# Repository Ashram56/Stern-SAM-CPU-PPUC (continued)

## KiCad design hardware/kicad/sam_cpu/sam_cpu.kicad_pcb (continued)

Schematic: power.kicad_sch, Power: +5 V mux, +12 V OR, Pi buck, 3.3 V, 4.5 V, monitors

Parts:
C1, C2: 100u; CP_Elec_8x10
C3, C9, C10: 100n; C_0603_1608Metric
C4, C8: 100u; CP_Elec_6.3x7.7
C5: 10u; C_0805_2012Metric
C6, C7, C133, C134: 10u; C_1206_3216Metric
C135, C136: 22u; C_1206_3216Metric
C137: 100n; C_0805_2012Metric
D1: SMBJ5.0CA; D_SMB
D2: green; LED_0603_1608Metric
D4: S1M; D_SMA
D5: SMBJ15A; D_SMB
F1: 4A hold; Fuse_2920_7451Metric
FB1: 6A; L_1206_3216Metric
J11: J11 POWER; Molex_KK-396_A-41791-0006_1x06_P3.96mm_Vertical
J17: EXT 5V; TerminalBlock_Phoenix_MKDS-1,5-2-5.08_1x02_P5.08mm_Horizont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
J23: EXT 12V; TerminalBlock_Phoenix_MKDS-1,5-2-5.08_1x02_P5.08mm_Horizont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
JP1: J11 5V; SolderJumper-2_P1.3mm_Bridged_RoundedPad1.0x1.5mm
JP3: PI 5V; PinHeader_1x03_P2.54mm_Horizontal
L2: 10u; L_Changjiang_FXL0630
Q19, Q20: DMP3013SFV; Diodes_PowerDI3333-8
R1: 100k; R_0603_1608Metric
R2: 33k; R_0805_2012Metric
R3: 1k; R_0603_1608Metric
R4, R5, R7, R214: 10k; R_0805_2012Metric
R6: 33k; R_0603_1608Metric
R213: 47k; R_0603_1608Metric
R215: 100k; R_0805_2012Metric
R216: 13k; R_0603_1608Metric
TP1: +5V; TestPoint_Pad_D1.5mm
TP2: +3V3; TestPoint_Pad_D1.5mm
TP3: +4V5; TestPoint_Pad_D1.5mm
TP4: +12V; TestPoint_Pad_D1.5mm
TP5, TP6: GND; TestPoint_Pad_D1.5mm
U1: TPS2117; SOT-583-8
U3: NCP1117-3.3; SOT-223-3_TabPin2
U33, U34: LTC4412; TSOT-23-6
U35: TPS54302; SOT-23-6

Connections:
+3V3: C7.1, R3.1, TP2.1, U3.2 (VO); also elsewhere on the board
+4V5: C8.1, D4.1 (K), TP3.1; also elsewhere on the board
+5V: C4.1, C5.1, C6.1, D4.2 (A), JP3.1 (A), R4.1, TP1.1, U1.2 (VOUT), U1.7 (VOUT), U3.3 (VI); also elsewhere on the board
+12V: C2.1, C3.1, C133.1, C134.1, D5.1 (K), F1.2, R6.1, TP4.1, U35.3 (VIN); also elsewhere on the board
/Power/12V_OR: F1.1, Q19.1 (S), Q19.2 (S), Q19.3 (S), Q20.1 (S), Q20.2 (S), Q20.3 (S), U33.6 (SENSE), U34.6 (SENSE)
/Power/EXT_5V: C1.1, D1.1 (A1), J17.1, R1.1, U1.3 (VIN1), U1.5 (MODE)
/Power/EXT_12V: J23.1, Q19.5 (D), R213.1, U33.1 (VIN)
/Power/IO_12V: J11.6, Q20.5 (D), U34.1 (VIN)
/Power/J11_5V: JP1.2 (B), U1.6 (VIN2)
/Power/PI_5V_BUCK: C135.1, C136.1, JP3.3 (B), L2.2, R215.1
GND: C1.2, C2.2, C3.2, C4.2, C5.2, C6.2, C7.2, C8.2, C9.2, C10.2, C133.2, C134.2, C135.2, C136.2, D1.2 (A2), D2.1 (K), D5.2 (A), J11.2, J11.4, J11.5, J17.2, J23.2, R2.2, R5.2, R7.2, R214.2, R216.2, TP5.1, TP6.1, U1.1 (GND), U3.1 (GND), U33.2 (GND), U33.3 (CTL), U34.2 (GND), U35.1 (GND); also elsewhere on the board
unnamed: D2.2 (A), R3.2
unnamed: FB1.1, J11.1
unnamed: FB1.2, JP1.1 (A)
unnamed: Q19.4 (G), U33.5 (GATE)
unnamed: Q20.4 (G), U34.5 (GATE)
unnamed: R1.2, R2.1, U1.4 (PR1)
unnamed: R213.2, R214.1, U34.3 (CTL)
unnamed: C137.1, U35.6 (BOOT)
unnamed: R215.2, R216.1, U35.4 (FB)
unnamed: C137.2, L2.1, U35.2 (SW)
PI_5V: JP3.2 (C); also elsewhere on the board
VMON_5V: C9.1, R4.2, R5.1; also elsewhere on the board
VMON_12V: C10.1, R6.2, R7.1; also elsewhere on the board

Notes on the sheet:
4.5 V for the switch matrix
External +12 V (J23) and rail fuse F1
Test points
Supply monitors (RP2354B ADC)
3.3 V
External +5 V (J17, priority)
J11 keeps the original CPU board connector (IO board J16 harness): +5 V, ground and +12 V (pin 6, unregulated); -12 V (pin 3) is not used. The +12 V rail (audio amplifiers, Pi buck) comes from J23 (external, priority) or J11 pin 6 through ideal diodes U33 / U34 (they block reverse polarity), then F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
IO board power (J11: +5 V, +12 V on pin 6)
+12 V OR (12V_OR to F1): J23 external (priority) or J11 pin 6 (IO board)
Pi 5.1 V buck (3 A) and Pi header 5 V jumper JP3
JP3 (3-pin header, one shunt) feeds J21 pins 2 / 4 (PI_5V) from one source: 1-2: the board +5 V 2-3: the buck (Pi 4 / Pi 5, 5.18 V 3 A) no shunt: Jetson, or a Pi on its own USB-C.

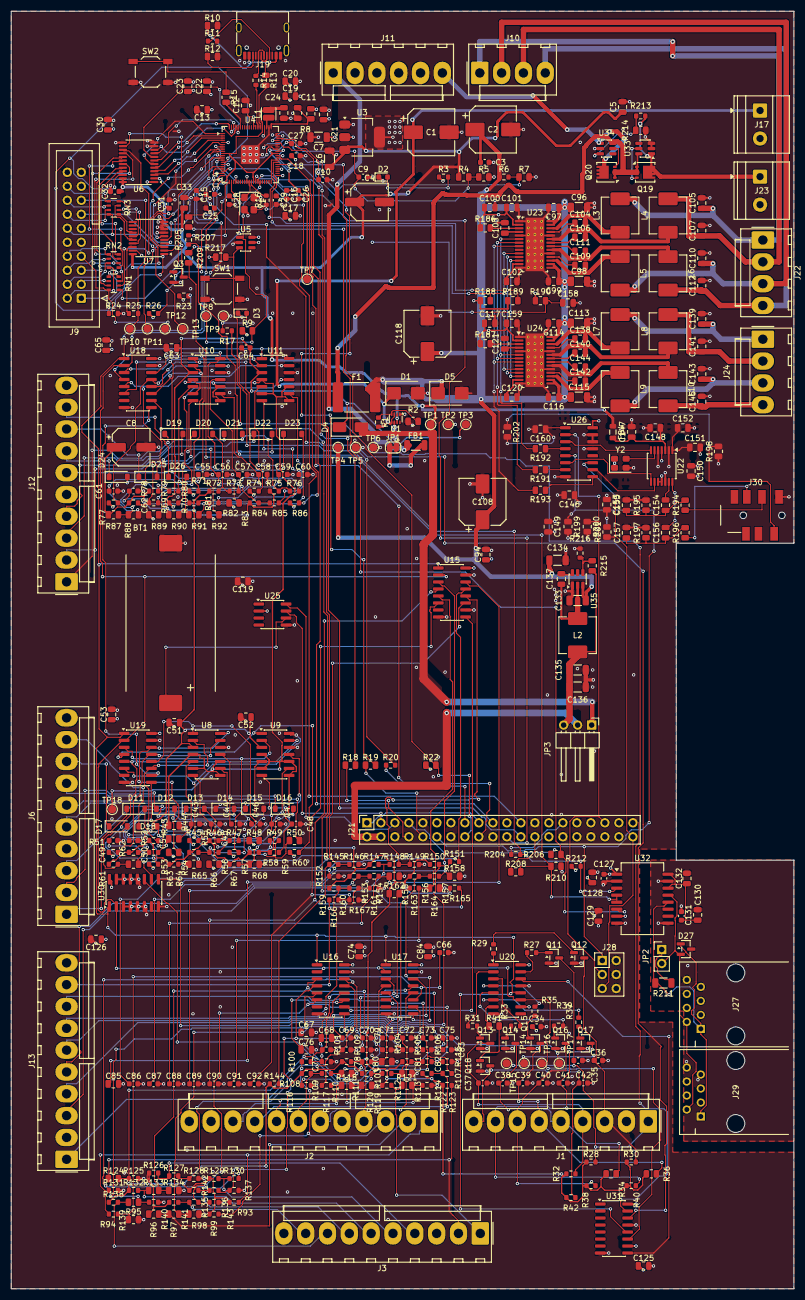
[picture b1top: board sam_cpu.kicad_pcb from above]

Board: 4 copper layers, 142.0 x 231.8 mm, 473 parts (0 on the bottom side), 320 nets.

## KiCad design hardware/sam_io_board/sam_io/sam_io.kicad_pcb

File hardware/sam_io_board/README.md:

# SAM_IO board: PPUC IO board for the Stern SAM IO power driver board

> **Revision 0.2 (branch `claude/sam-io-rp2354-dedicated`): schematic and two routed PCB options.**
> - `sam_io/`: 158 x 100 mm. J13, J3 and J2 sit on the original CPU board harness spots.
> - `sam_io_100mm/`: 100 x 100 mm. J13 on the original spot, J3 3.5 mm lower than the original spot (toward the bottom edge, for room under J2), J2 moved inboard above J3. Same schematic.
>
> Both boards put the bottom-left corner on the CPU board's bottom-left corner, with the KK-396 ramps facing inward.
> On both boards J9 stands on the left edge above J13, turned like the CPU board's J9 (pin 1 at the bottom, odd pins
> and the key notch toward the board centre), so the IO board ribbon arrives from the same side as before.
> The RP2040 and its W25Q flash are replaced by an **RP2354B** (QFN-80, 2 MB internal flash), and a new sheet
> "Dedicated switches" adds the SAM CPU board's harness connectors **J2, J3 and J13** (KK-396) with 17 input
> stages: J3 D9-D16 (flippers, EOS), J13 D17-D24 (tilt, slam, ticket notch, D20, BACK, MINUS, PLUS, SELECT) and
> the coin door memory protect on J2 pin 10. The coin slots (J2 D1-D8) are not routed. The SWD header J3 is
> renamed J20. Details: [`DESIGN.md` section 0](DESIGN.md#0-revision-02-rp2354b-and-dedicated-switches). The
> renders `sam_io/pcb_render.png` and `sam_io_100mm/pcb_render.png` show revision 0.2; the rest of this file still
> describes revision 0.1 (RP2040, 100 x 70 mm PCB).

A PPUC IO board (RP2040 on RS485) that drives a Stern SAM IO power driver board (520-5249-00) through its
CPU connector J1. It is the hardware for the `SAM_IO` board type (`PPUC_BOARD_TYPE=5`) in the io-boards
firmware (Ashram56/io-boards PR #1, `src/IODevices/SamBus/`): one board forwards every coil, flasher and lamp
of the machine to the SAM IO board's registers. It has no switch inputs and no output stage of its own.

It is derived from the PPUC **IO_16_8_1** board, version 1.1.1, by foenich
(<https://github.com/PPUC/Hardware_IO_16_8_1>, commit `46e0c47`), licensed under the
**TAPR Open Hardware License 1.0**. See [Licence](#licence-and-change-notice) below.

- [`DESIGN.md`](DESIGN.md): detailed design notes (circuit, power, reset, bus timing, signal list, BOM, PCB,
  manufacturing, bring-up).
- `sam_io/`: the KiCad 10 project (10.0 file format). Open `sam_io.kicad_pro`.
- `sam_io_100mm/`: the same project with the 100 x 100 mm board (J2 inboard).
- `sam_io_krt/`: an experiment, the same board stripped and routed again from scratch with KiCadRoutingTools,
  with a side-by-side comparison. Not the board to build.
- `sam_io/sam_io_bom.csv`: bill of materials, grouped by value and footprint.
- `sam_io/sam_io.pdf`: the two schematic sheets, for reading without KiCad.
- `sam_io/pcb_render.png`: top view of the routed board; `sam_io/pcb_copper.png`: its copper (F.Cu red, B.Cu blue).
- `original/`: the unmodified IO_16_8_1 v1.1.1 files this design was made from (KiCad 6), its PDF schematic,
  README and change log.
- `tools/`: the scripts that made the changes, for the record (see the end of this file). From now on the
  KiCad files are the source of truth: edit them in KiCad.

## What changed from IO_16_8_1

| | IO_16_8_1 | SAM_IO |
|---|---|---|
| High-power outputs (sheet OUT8) | 8 MOSFET outputs, flyback diodes, F2, 3300 µF C56, J9-J11 | **removed** |
| Inputs (sheet IN16) | 16 inputs with 2N7002 level shifters, J6-J8 | **removed**: GPIO3-18 are the SAM bus |
| SAM bus (new sheet "SAM bus") | | J9 2x10 header, SN74LVC8T245, 74AHCT541, 2N7002 for NBRESET |
| RP2040, flash, crystal, USB-C J4, SWD J3, reset / boot buttons | | unchanged |
| RS485 (ADM3483, J1, JP1-JP3 bias / termination) | | unchanged, except the 0 ohm R9 (RO to GPIO1) is now a track |
| QWIIC J2, its pull-ups R96 / R97 and C8 | | **removed** (2026-10-08) |
| Power J5 (5 V in), AP2112 3.3 V, address DIP SW3 + ladder on GPIO28, LED on GPIO25 | | unchanged |
| Special output (GPIO29 through SN74AHCT1G125 to J5 pin 5) | | unchanged (the SAM_IO firmware does not use it) |

Every part that stays keeps its reference, its position on the board and its routing.

The board is **100 x 70 mm**, the size of the PPUC Opto_16 board (99.7 x 67.3 mm) plus 2.7 mm, because the
address DIP switch SW3 sits that low on IO_16_8_1. The lower 30 mm of IO_16_8_1 held only the output stage.
The four 5.5 mm mounting holes stay at the corners, 5 mm from the edges (the top two did not move, the
bottom two moved up to y = 104 mm). They are not Opto_16's hole pattern.

## Connectors

The kept connectors are the same parts as on IO_16_8_1:

| Ref | Part | Use |
|---|---|---|
| J1 | 6-way RTM push-in terminal | RS485: 1 A, 2 B, 3 SHD, 4 A, 5 B, 6 GND (unchanged) |
| J5 | 6-way RTM push-in terminal | 1, 3, 4 = +5 V in, 2, 6 = GND, 5 = special output (unchanged) |
| J4 | USB-C | programming and debug |
| J3 | 1x3 2.54 mm (not fitted) | SWD |
| **J9** | **2x10 2.54 mm shrouded IDC header** | **SAM bus to the SAM IO board J1** |

J9 is the only new connector. It has the SAM IO board J1 pinout pin for pin, the same as J9 on the SAM CPU
replacement board, so a straight 20-way IDC ribbon (pin 1 to pin 1) connects the two:

| J9 pin | Signal | J9 pin | Signal |
|---|---|---|---|
| 1 | D3 | 2 | D4 |
| 3 | D2 | 4 | D5 |
| 5 | D1 | 6 | D6 |
| 7 | D0 | 8 | D7 |
| 9 | n.c. | 10 | n.c. |
| 11 | n.c. | 12 | A0 |
| 13 | NBRESET (open drain, active low) | 14 | A1 |
| 15 | IOSTB (active low) | 16 | A2 |
| 17 | n.c. | 18 | A3 |
| 19 | GND | 20 | GND |

The SAM IO board's J1 carries no supply, so this board is powered from J5 like every PPUC board.

## SAM bus circuit and GPIO map

The "SAM bus" sheet is a copy of the IO bus sheet of the SAM CPU replacement board
(`hardware/kicad/sam_cpu/io_bus.kicad_sch`, docs/ARCHITECTURE.md 3.1-3.2), so both boards that can drive a
SAM IO board use the same circuit:

- D0-D7: SN74LVC8T245 (U7), A side 3.3 V, B side 5 V. DIR comes from the firmware (1 = this board drives J9),
  10 k pull-down (R28).
- A0-A3 and IOSTB: 74AHCT541 (U8) at 5 V, TTL inputs. Unused inputs tied low.
- Both buffers share BUS_OE_N with a 10 k pull-up (R27): off at power-up, so the SAM IO board's own pull-ups
  hold IOSTB high and nothing latches while the RP2040 boots.
- NBRESET: 2N7002 (Q1) open drain against the SAM IO board's 10 k pull-up. Its gate has a 10 k pull-up (R30),
  so the SAM IO board is held in reset (all outputs off) until the firmware lets go.
- 33 R in series on every J9 line (RN1-RN3, R29), for the ribbon cable.
- Test points TP3 IOSTB, TP4 NBRESET, TP5 D0, TP6 A0.

The GPIOs match `src/IODevices/SamBus/SamBusPins.h` in io-boards exactly, so the firmware needs no change:

| GPIO | Signal | GPIO | Signal |
|---|---|---|---|
| 0, 1, 2 | RS485 TX, RX, DE (unchanged) | 15 | BUS_IOSTB |
| 3-10 | BUS_D0-D7 | 16 | BUS_DIR |
| 11-14 | BUS_A0-A3 | 17 | BUS_OE_N (low = buffers on) |
| 25 | status LED (unchanged) | 18 | NBRESET_DRV (high = SAM IO board in reset) |
| 28 | board id ladder, DIP SW3 (unchanged) | 29 | special output (unchanged) |
| 19-24, 26, 27 | not connected (were Out_1-Out_8) | | |

Revision 0.2 (RP2354B) keeps GPIO0-18, 25 and 29 as above and adds:

| GPIO | Signal | GPIO | Signal |
|---|---|---|---|
| 19-24, 26, 27 | DED_D17-D24 (J13: tilt, slam, ticket notch, D20, BACK, MINUS, PLUS, SELECT) | 38 | MEM_PROTECT (J2 pin 10, coin door) |
| 30-37 | DED_D9-D16 (J3: flipper buttons and EOS) | 40 (ADC0) | board id ladder, DIP SW3 (was GPIO28: the RP2354B's ADC is on GPIO40-47) |
| 28, 39, 41-47 | not connected | | |

All dedicated inputs are active low (switch closed = 0).

## Checks

- ERC (KiCad 10.0.6): 2 errors and 9 warnings, all inherited from IO_16_8_1 (ADC_AVDD and +5 V power-flag
  warnings, +5 V / VCC net name on U5, library symbols that differ from the KiCad 10 libraries). Nothing on the
  new sheet.
- The netlist was compared pin by pin with the original: every kept part keeps its nets, except the RP2040
  GPIO3-18 (now the bus) and GPIO19-24, 26, 27 (now unconnected).
- DRC: fully routed (no unconnected item), no new violation. The remaining items are the original's (USB-C J4
  pad to slot clearance, J2 / C8 courtyards, starved thermals on J4, U5 and C8, footprints that differ from the
  KiCad 10 libraries). Design rules are unchanged: 0.2 mm tracks and clearance, 0.5 / 0.3 mm vias.
- Schematic parity: no net differences. KiCad lists field differences (datasheet links, test point BOM flag)
  that one "Update PCB from Schematic" in KiCad clears.

## Open points

Nothing below blocks reviewing the design; the first group blocks ordering boards, the rest is to check on the
bench or to tidy up later. [DESIGN.md](DESIGN.md) has the details behind each one.

Before ordering:

- **Fabrication files**: no Gerbers, drill files or pick-and-place file yet. Generate them from KiCad (or
  `kicad-cli pcb export gerbers / drill / pos`) once the points below are settled.
- **Update PCB from Schematic**: run it once in KiCad to clear the remaining field differences (datasheet links,
  test point BOM flag). No net changes are expected; re-run DRC afterwards.
- **C31 via in pad**: there was no room for a GND via beside C31 (U7's 5 V decoupling), so its GND pad has
  one. Ask the fab for a filled or tented via, or check the solder joint.
- **Mounting holes**: the four corner holes of the 100 x 70 mm outline follow neither IO_16_8_1 nor Opto_16.
  Check where the board will sit in the machine (or on the SAM IO board's ribbon) and move them if needed.
- **Parts availability**: check stock for the new parts (SN74LVC8T245 in TSSOP-24, 74AHCT541 in TSSOP-20, 2N7002,
  4 x 33 R arrays, 2 x 10 IDC header) at the assembler; the BOM is `sam_io/sam_io_bom.csv`.

On the bench:

- **Bus timing against a real SAM IO board** (ARCHITECTURE.md Q4): setup, IOSTB width and hold as set by the
  firmware (140 / 175 / 245 ns), the STATUS read turnaround (DIR flip and U7 delay inside the read window),
  and edge quality on the 22 pF lines through the series resistors.
- **Watchdog and reset**: the SAM IO board must stay in reset while the RP2040 boots and come out of it only
  once lamp strobes run (DRV0 within 62.5-250 ms); NBRESET held low long enough for the DS1232 (about 20 ms).
- **Ribbon**: the 20-way cable carries only two GND wires; keep it short, check pin-1 orientation on both ends
  and the ground return under full lamp load.
- **5 V supply**: confirm which 5 V the board takes in the machine and that its ground is shared with the SAM
  IO board's logic ground.
- **Firmware**: the `SAM_IO` board type is in Ashram56/io-boards PR #1, still open. Board type `0x05` is a
  proposal to agree with PPUC upstream.

Later, if wanted:

- **References reused**: J9, Q1, R27-R30 and C30-C33 were IO_16_8_1 input / output parts and are now SAM bus
  parts (matching the CPU board's J9). Compare with `original/` by function, not by reference. A re-annotation
  would remove the confusion but break the comparison.
- **Spare resources**: RP2040 GPIO19-24, 26, 27 are unconnected and U8 has three unused channels (inputs tied
  to GND). They could carry the 20 V / 50 V interlock inputs or GI relay control later.
- **Library footprints**: several footprints inherited from IO_16_8_1 differ from the KiCad 10 libraries (DRC
  warnings only). Update them from the library if the board is reworked.
- **Copper tidy-up**: a few short GND tracks between stitching vias on B.Cu are left from IO_16_8_1's routing;
  harmless inside the pour, removable.

## Routing

Two layers, as on IO_16_8_1. The parts that stayed keep their routing; the SAM bus parts sit on the left, where
the input stage was:

- J9 on the left edge, RN1-RN3 and R29 next to it, then U7 (data) above U8 (address and IOSTB), close to the
  RP2040.
- RP2040 to buffers, routed by hand (`tools/c08_bus_fanout.py`). The RP2040 and both buffers number their pins
  anticlockwise, so a bus that keeps its bit order between them has to cross itself once. Each of the 13 lines
  leaves the RP2040 on the top layer (reusing IO_16_8_1's GPIO fanout next to the chip), drops through a via
  under its own buffer pin and crosses under the others on the bottom layer, then comes back up to the pin:
  two vias per line. DIR, OE_N and NBRESET_DRV reuse IO_16_8_1's GPIO16-18 fanout down the right of the RP2040.
- Buffers to J9, pull-ups and power: Freerouting 2.5, with every existing track locked, then a few touch-ups
  (`tools/c09_route_fixes.py`).
- GND is the pour on both layers, as before.

## Licence and change notice

This design is a modification of PPUC IO_16_8_1 v1.1.1 by foenich and is licensed, like the original, under the
**TAPR Open Hardware License 1.0** ([`LICENSE-TAPR-OHL.txt`](LICENSE-TAPR-OHL.txt), an unaltered copy). It is
not covered by the repository's CERN-OHL-S licence. The modifications are licensed under the terms of the TAPR
OHL.

Elements changed (TAPR OHL 4.2a):
- `IO_16_8_1.kicad_sch` -> `sam_io/sam_io.kicad_sch`: IN16 and OUT8 sheets and their labels removed; GPIO3-18
  labels renamed to the SAM bus global labels; no-connect flags on GPIO19-24, 26, 27; "SAM bus" sheet added;
  title block and a change note; file upgraded to KiCad 10.
- `IN16.kicad_sch`, `OUT8.kicad_sch`: removed.
- `sam_io/sam_bus.kicad_sch`: new (from the SAM CPU replacement board's IO bus sheet).
- `IO_16_8_1.kicad_pcb` -> `sam_io/sam_io.kicad_pcb`: IN16 / OUT8 footprints, their tracks and vias, the GNDPWR
  zone and the J6-J11 / fuse silkscreen removed; GND zone extended over the freed area; board name changed to
  "PPUC SAM_IO"; SAM bus parts added and routed; outline cut to 100 x 70 mm, bottom mounting holes, logo and
  board name moved up, copper below the new edge removed; file upgraded to KiCad 10.
- `IO_16_8_1.kicad_pro` -> `sam_io/sam_io.kicad_pro`: renamed, upgraded to KiCad 10.
- `logo.kicad_sym`, `IO_16_8_1.pretty`, `fp-lib-table`, `sym-lib-table`, `PPUC-Logo-PCB-230129.svg`: unchanged.

The original versions of the changed files are in `original/` (TAPR OHL 4.2b). The original documentation names
no licensor e-mail address, so section 3 asks nothing further. Before boards are made, add the Gerber and drill
files to this folder (TAPR OHL 4.2d).

## How the changes were made

`tools/c01_root_sheet.py` and `tools/c02_sam_bus_sheet.py` edited the schematic sheets.
`tools/run.sh` rebuilt the board from the original with `c03_board_update.py` (remove / add footprints, KiCad 10
Python), `c04_board_clean.py` (tracks, zones and silkscreen, on the file text) and `c05_drc_via_cleanup.py`
(leftover vias reported by DRC). `tools/run_route.sh` then made the 100 x 70 mm outline and the routing:
`c06_outline_placement.py` (outline, holes, placement), `c07_trim_copper.py` (copper below the new edge),
`c08_bus_fanout.py` (RP2040 side of the bus), two Freerouting passes (`route_mkdsn.py`, `route_import.py`),
`c09_route_fixes.py` and `c10_silk.py`. Do not rerun them over the current files.

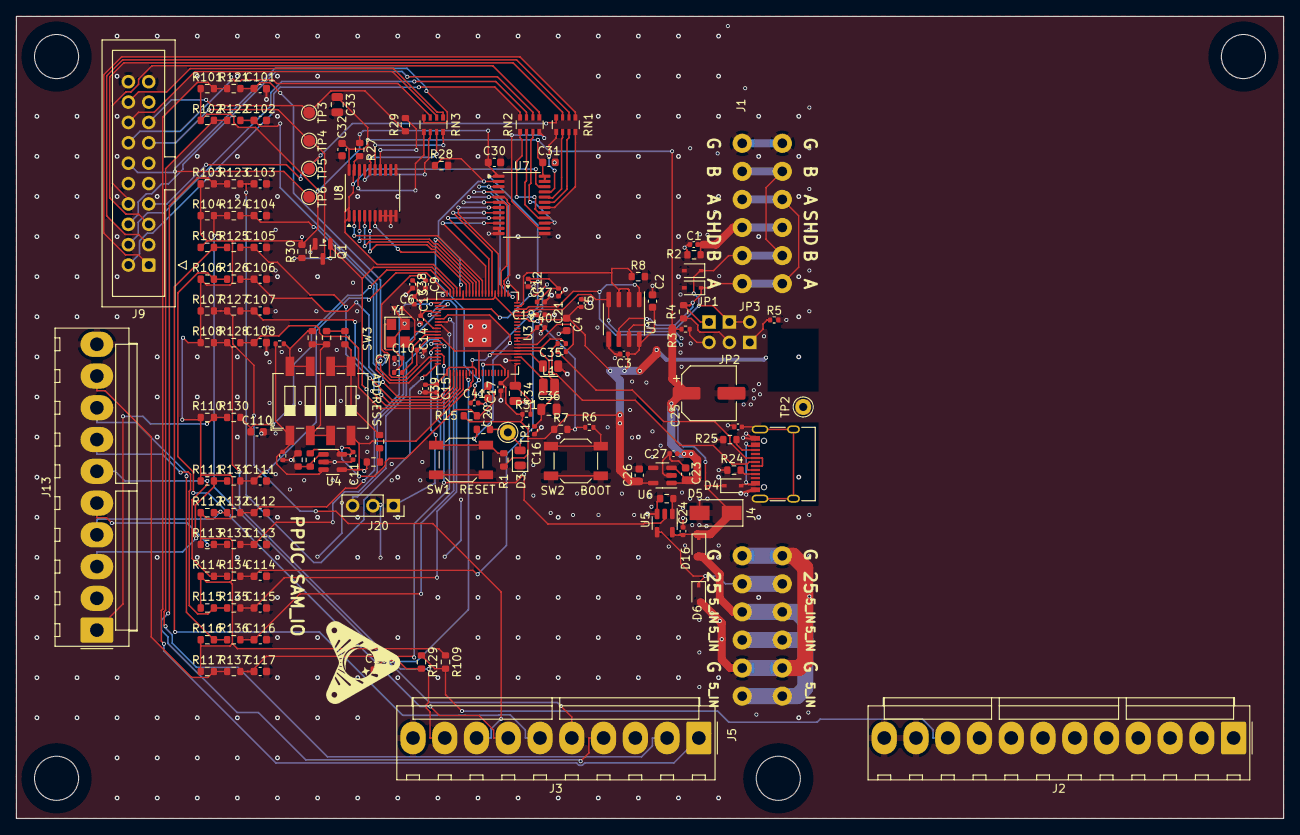
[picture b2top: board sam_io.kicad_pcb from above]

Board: 2 copper layers, 158.0 x 100.0 mm, 158 parts (0 on the bottom side), 123 nets.

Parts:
C1, C3, C5, C9, C10, C11, C12, C13, C14, C15, C17, C19, C22, C24, C27, C37, C38, C39, C40, C41: 100n; C_0402_1005Metric
C2, C4, C20, C23, C26: 10u; C_0603_1608Metric
C6, C7: 27pF; C_0402_1005Metric
C16, C21: 1u; C_0402_1005Metric
C25: 100µ 16V; CP_Elec_6.3x5.4
C30, C31, C32: 100n; C_0603_1608Metric
C33: 10u; C_0805_2012Metric
C34, C35, C36: 4.7u; C_0805_2012Metric
C101, C102, C103, C104, C105, C106, C107, C108, C109, C110, C111, C112, C113, C114, C115, C116, C117: 1n; C_0603_1608Metric
D1, D2: SD15; D_SOD-323
D3: LED gn; LED_0805_2012Metric
D4, D16: 1A; D_SOD-323
D5: SMAJ5.0; D_SMA
D6: SD05; D_SOD-323
J1, J5: Conn_01x06; Terminal_Block_RTMPin
J2: J2 DEDICATED D1-D8; Molex_KK-396_A-41791-0012_1x12_P3.96mm_Vertical
J3: J3 DEDICATED D9-D16; Molex_KK-396_A-41791-0010_1x10_P3.96mm_Vertical
J4: USB_C_Receptacle_USB2.0; USB_C_Receptacle_XKB_U262-16XN-4BVC11
J9: SAM BUS; IDC-Header_2x10_P2.54mm_Vertical
J13: J13 DEDICATED D17-D24; Molex_KK-396_A-41791-0010_1x10_P3.96mm_Vertical
J20: nmount SW Debug; PinSocket_1x03_P2.54mm_Vertical
JP1, JP2, JP3: Jumper_2_Open; PinHeader_1x02_P2.54mm_Vertical
L1: 3.3u; L_Cenker_CKCS201610
Q1: 2N7002; SOT-23
R1, R7, R8, R26, R27, R28, R30, R121, R122, R123, R124, R125, R126, R127, R128, R129, R130, R131, R132, R133, R134, R135, R136, R137: 10k; R_0603_1608Metric
R2, R15: 100R; R_0603_1608Metric
R3, R5: 620; R_0402_1005Metric
R4: 120R; R_0603_1608Metric
R6, R12, R16, R20: 1k; R_0402_1005Metric
R10, R11: 27; R_0402_1005Metric
R13: 33k; R_0603_1608Metric
R14, R18, R19, R23: 2k; R_0603_1608Metric
R17: 5k; R_0603_1608Metric
R21: 470; R_0603_1608Metric
R22: 3k; R_0603_1608Metric
R24, R25: 5k1; R_0603_1608Metric
R29: 33; R_0603_1608Metric
R31: 33; R_0402_1005Metric
R101, R102, R103, R104, R105, R106, R107, R108, R109, R110, R111, R112, R113, R114, R115, R116, R117: 1k; R_0603_1608Metric
RN1, RN2, RN3: 33; R_Array_Convex_4x0603
SW1: Reset; SW_SPST_SKQG_WithStem
SW2: Boot; SW_SPST_SKQG_WithStem
SW3: ADDRESS; SW_DIP_SPSTx04_Slide_6.7x11.72mm_W8.61mm_P2.54mm_LowProfile
TP1: TP_LED; Pin_D1.0mm_L10.0mm
TP2: TP_GND; Pin_D1.0mm_L10.0mm
TP3: J9_IOSTB; TestPoint_Pad_D1.5mm
TP4: J9_NBRESET; TestPoint_Pad_D1.5mm
TP5: J9_D0; TestPoint_Pad_D1.5mm
TP6: J9_A0; TestPoint_Pad_D1.5mm
U1: ADM3483; SOIC-8_3.9x4.9mm_P1.27mm
U3: RP2354B; QFN-80-1EP_10x10mm_P0.4mm_EP3.4x3.4mm
U4: LMV321; SOT-23-5
U5: SN74AHCT1G125; SOT-23-5
U6: AP2112K-3.3; SOT-23-5
U7: SN74LVC8T245; TSSOP-24_4.4x7.8mm_P0.65mm
U8: 74AHCT541; TSSOP-20_4.4x6.5mm_P0.65mm
Y1: 12MHz,18pF; Crystal_SMD_3225-4Pin_3.2x2.5mm

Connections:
+3V3: C2.1, C3.1, C4.1, C5.1, C12.1, C13.1, C14.1, C15.1, C17.1, C19.1, C21.1, C26.1, C30.1, C35.1, C37.1, C38.1, C39.1, C40.1, R1.2, R7.1, R15.1, R27.1, R30.1, R31.1, R101.1, R102.1, R103.1, R104.1, R105.1, R106.1, R107.1, R108.1, R109.1, R110.1, R111.1, R112.1, R113.1, R114.1, R115.1, R116.1, R117.1, U1.8 (VCC), U3.5, U3.15, U3.24, U3.29, U3.41, U3.50, U3.60, U3.64, U3.68, U3.69, U3.76, U6.5 (VOUT), U7.1
+5V: C23.1, C24.1, C25.1, C27.1, C31.1, C32.1, C33.1, D4.1 (K), D5.1 (K), D16.1 (K), R3.1, U5.5 (VCC), U6.1 (VIN), U6.3 (EN), U7.23, U7.24, U8.20
/1V1: C9.1, C10.1, C16.1, C36.1, C41.1, L1.2, U3.10, U3.32, U3.51, U3.65
/3V3A: C11.1, C20.1, R13.1, R15.2, U3.59, U4.5 (V+)
/5V_IN: D16.2 (A), J5.1, J5.3, J5.4
/485_DE: R8.2, U1.2 (~RE), U1.3 (DE), U3.79
/485_RX: U1.1 (RO), U3.78
/485_TX: U1.4 (DI), U3.77
/A: D1.1 (K), J1.1, J1.4, JP1.1 (A), R4.1, U1.6 (A)
/B: D2.1 (K), J1.2, J1.5, JP2.1 (A), JP3.2 (B), U1.7 (B)
/Dedicated switches/IN_D9: J3.1, R101.2, R121.1
/Dedicated switches/IN_D10: J3.2, R102.2, R122.1
/Dedicated switches/IN_D11: J3.4, R103.2, R123.1
/Dedicated switches/IN_D12: J3.5, R104.2, R124.1
/Dedicated switches/IN_D13: J3.6, R105.2, R125.1
/Dedicated switches/IN_D14: J3.7, R106.2, R126.1
/Dedicated switches/IN_D15: J3.8, R107.2, R127.1
/Dedicated switches/IN_D16: J3.9, R108.2, R128.1
/Dedicated switches/IN_D17: J13.1, R110.2, R130.1
/Dedicated switches/IN_D18: J13.3, R111.2, R131.1
/Dedicated switches/IN_D19: J13.4, R112.2, R132.1
/Dedicated switches/IN_D20: J13.5, R113.2, R133.1
/Dedicated switches/IN_D21: J13.6, R114.2, R134.1
/Dedicated switches/IN_D22: J13.7, R115.2, R135.1
/Dedicated switches/IN_D23: J13.8, R116.2, R136.1
/Dedicated switches/IN_D24: J13.9, R117.2, R137.1
/Dedicated switches/IN_MEMPROT: J2.10, R109.2, R129.1
/Out_S: D6.1 (K), J5.5, U5.4
/Out_Special: U3.37, U5.2
/Q_nCS: R6.2, R7.2, U3.75
/SHD: C1.1, J1.3, R2.1
/SWCLK: J20.1, U3.33
/SWDIO: J20.3, U3.34
/USB_D+: J4.A6 (D+), J4.B6 (D+), R10.1
/USB_D-: J4.A7 (D-), J4.B7 (D-), R11.1
/USB_DM_MCU: R11.2, U3.66
/USB_DP_MCU: R10.2, U3.67
/VREG_AVDD: C34.1, R31.2, U3.61
/VREG_LX: L1.1, U3.63
/V_addr: R17.1, SW3.4, U3.49, U4.4
/XIN: C6.2, U3.30, Y1.3
/XOUT: R12.2, U3.31
/nReset: R1.1, SW1.2, U3.35
BUS_A0: U3.9, U8.2
BUS_A1: U3.11, U8.3
BUS_A2: U3.12, U8.4
BUS_A3: U3.13, U8.5
BUS_D0: U3.80, U7.3
BUS_D1: U3.1, U7.4
BUS_D2: U3.2, U7.5
BUS_D3: U3.3, U7.6
BUS_D4: U3.4, U7.7
BUS_D5: U3.6, U7.8
BUS_D6: U3.7, U7.9
BUS_D7: U3.8, U7.10
BUS_DIR: R28.1, U3.16, U7.2
BUS_IOSTB: U3.14, U8.6
BUS_OE_N: R27.2, U3.17, U7.22, U8.1, U8.19
DED_D9: C101.1, R121.2, U3.38
DED_D10: C102.1, R122.2, U3.39
DED_D11: C103.1, R123.2, U3.40
DED_D12: C104.1, R124.2, U3.42
DED_D13: C105.1, R125.2, U3.43
DED_D14: C106.1, R126.2, U3.44
DED_D15: C107.1, R127.2, U3.45
DED_D16: C108.1, R128.2, U3.46
DED_D17: C110.1, R130.2, U3.19
DED_D18: C111.1, R131.2, U3.20
DED_D19: C112.1, R132.2, U3.21
DED_D20: C113.1, R133.2, U3.22
DED_D21: C114.1, R134.2, U3.23
DED_D22: C115.1, R135.2, U3.25
DED_D23: C116.1, R136.2, U3.27
DED_D24: C117.1, R137.2, U3.28
GND: C1.2, C2.2, C3.2, C4.2, C5.2, C6.1, C7.1, C9.2, C10.2, C11.2, C12.2, C13.2, C14.2, C15.2, C16.2, C17.2, C19.2, C20.2, C21.2, C22.2, C23.2, C24.2, C25.2, C26.2, C27.2, C30.2, C31.2, C32.2, C33.2, C34.2, C35.2, C36.2, C37.2, C38.2, C39.2, C40.2, C41.2, C101.2, C102.2, C103.2, C104.2, C105.2, C106.2, C107.2, C108.2, C109.2, C110.2, C111.2, C112.2, C113.2, C114.2, C115.2, C116.2, C117.2, D1.2 (A), D2.2 (A), D3.1 (K), D5.2 (A), D6.2 (A), J1.6, J2.11, J2.12, J3.10, J4.A1 (GND), J4.A12 (GND), J4.B1 (GND), J4.B12 (GND), J5.2, J5.6, J9.19, J9.20, J13.10, J20.2, Q1.2, R2.2, R5.2, R8.1, R14.2, R16.2, R24.2, R25.2, R26.2, R28.2, SW1.1, SW2.1, TP2.1, U1.5 (GND), U3.62, U3.81, U4.2 (V-), U5.3 (GND), U6.2 (GND), U7.11, U7.12, U7.13, U8.7, U8.8, U8.9, U8.10, Y1.2, Y1.4
MEM_PROTECT: C109.1, R129.2, U3.47
NBRESET_DRV: Q1.1, R30.2, U3.18
unnamed: C7.2, R12.1, Y1.1
unnamed: D3.2 (A), R21.2, TP1.1
unnamed: D4.2 (A), J4.A4 (VBUS), J4.A9 (VBUS), J4.B4 (VBUS), J4.B9 (VBUS)
unnamed: J4.A5 (CC1), R24.1
unnamed: J4.B5 (CC2), R25.1
unnamed: C22.1, J4.S1 (SHIELD)
unnamed: J9.1, RN1.1
unnamed: J9.2, RN2.4
unnamed: J9.3, RN1.2
unnamed: J9.4, RN2.3
unnamed: J9.5, RN1.3
unnamed: J9.6, RN2.2
unnamed: J9.7, RN1.4, TP5.1
unnamed: J9.8, RN2.1
unnamed: J9.12, RN3.4, TP6.1
unnamed: J9.13, Q1.3, TP4.1
unnamed: J9.14, RN3.3
unnamed: J9.15, R29.2, TP3.1
unnamed: J9.16, RN3.2
unnamed: J9.18, RN3.1
unnamed: JP1.2 (B), R3.2
unnamed: JP2.2 (B), R4.2
unnamed: JP3.1 (A), R5.1
unnamed: R6.1, SW2.2
unnamed: R17.2, R22.1
unnamed: R18.1, R19.1, SW3.2, SW3.3
unnamed: R18.2, R23.1
unnamed: R19.2, R20.2, SW3.7, SW3.8
unnamed: R22.2, R23.2, SW3.5, SW3.6
unnamed: R26.1, U5.1
unnamed: RN1.8, U7.18
unnamed: RN1.7, U7.19
unnamed: RN1.6, U7.20
unnamed: RN1.5, U7.21
unnamed: RN2.8, U7.14
unnamed: RN2.7, U7.15
unnamed: RN2.6, U7.16
unnamed: RN2.5, U7.17
unnamed: RN3.8, U8.15
unnamed: RN3.7, U8.16
unnamed: RN3.6, U8.17
unnamed: RN3.5, U8.18
unnamed: R21.1, U3.26
unnamed: R13.2, R14.1, U4.1 (+)
unnamed: R16.1, R20.1, SW3.1, U4.3 (-)
unnamed: R29.1, U8.14

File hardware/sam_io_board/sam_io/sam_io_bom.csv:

"Reference","Value","Footprint","QUANTITY","Datasheet"
"C1,C3,C5,C9,C10,C11,C12,C13,C14,C15,C17,C19,C22,C24,C27,C37,C38,C39,C40,C41","100n","Capacitor_SMD:C_0402_1005Metric","20",""
"C2,C4,C20,C23,C26","10u","Capacitor_SMD:C_0603_1608Metric","5",""
"C6,C7","27pF","Capacitor_SMD:C_0402_1005Metric","2",""
"C16,C21","1u","Capacitor_SMD:C_0402_1005Metric","2",""
"C25","100µ 16V","Capacitor_SMD:CP_Elec_6.3x5.4","1",""
"C30,C31,C32","100n","Capacitor_SMD:C_0603_1608Metric","3",""
"C33","10u","Capacitor_SMD:C_0805_2012Metric","1",""
"C34,C35,C36","4.7u","Capacitor_SMD:C_0805_2012Metric","3",""
"C101,C102,C103,C104,C105,C106,C107,C108,C109,C110,C111,C112,C113,C114,C115,C116,C117","1n","Capacitor_SMD:C_0603_1608Metric","17",""
"D1,D2","SD15","Diode_SMD:D_SOD-323","2",""
"D3","LED gn","LED_SMD:LED_0805_2012Metric","1",""
"D4,D16","1A","Diode_SMD:D_SOD-323","2",""
"D5","SMAJ5.0","Diode_SMD:D_SMA","1",""
"D6","SD05","Diode_SMD:D_SOD-323","1",""
"J1,J5","Conn_01x06","IO_16_8_1:Terminal_Block_RTMPin","2",""
"J2","J2 DEDICATED D1-D8","Connector_Molex:Molex_KK-396_A-41791-0012_1x12_P3.96mm_Vertical","1",""
"J3","J3 DEDICATED D9-D16","Connector_Molex:Molex_KK-396_A-41791-0010_1x10_P3.96mm_Vertical","1",""
"J4","USB_C_Receptacle_USB2.0","Connector_USB:USB_C_Receptacle_XKB_U262-16XN-4BVC11","1","https://www.usb.org/sites/default/files/documents/usb_type-c.zip"
"J9","SAM BUS","Connector_IDC:IDC-Header_2x10_P2.54mm_Vertical","1",""
"J13","J13 DEDICATED D17-D24","Connector_Molex:Molex_KK-396_A-41791-0010_1x10_P3.96mm_Vertical","1",""
"JP1,JP2,JP3","Jumper_2_Open","Connector_PinHeader_2.54mm:PinHeader_1x02_P2.54mm_Vertical","3",""
"L1","3.3u","Inductor_SMD:L_Cenker_CKCS201610","1",""
"Q1","2N7002","Package_TO_SOT_SMD:SOT-23","1","https://www.onsemi.com/pub/Collateral/NDS7002A-D.PDF"
"R1,R7,R8,R26,R27,R28,R30,R121,R122,R123,R124,R125,R126,R127,R128,R129,R130,R131,R132,R133,R134,R135,R136,R137","10k","Resistor_SMD:R_0603_1608Metric","24",""
"R2,R15","100R","Resistor_SMD:R_0603_1608Metric","2",""
"R3,R5","620","Resistor_SMD:R_0402_1005Metric","2",""
"R4","120R","Resistor_SMD:R_0603_1608Metric","1",""
"R6,R12,R16,R20","1k","Resistor_SMD:R_0402_1005Metric","4",""
"R10,R11","27","Resistor_SMD:R_0402_1005Metric","2",""
"R13","33k","Resistor_SMD:R_0603_1608Metric","1",""
"R14,R18,R19,R23","2k","Resistor_SMD:R_0603_1608Metric","4",""
"R17","5k","Resistor_SMD:R_0603_1608Metric","1",""
"R21","470","Resistor_SMD:R_0603_1608Metric","1",""
"R22","3k","Resistor_SMD:R_0603_1608Metric","1",""
"R24,R25","5k1","Resistor_SMD:R_0603_1608Metric","2",""
"R29","33","Resistor_SMD:R_0603_1608Metric","1",""
"R31","33","Resistor_SMD:R_0402_1005Metric","1",""
"R101,R102,R103,R104,R105,R106,R107,R108,R109,R110,R111,R112,R113,R114,R115,R116,R117","1k","Resistor_SMD:R_0603_1608Metric","17",""
"RN1,RN2,RN3","33","Resistor_SMD:R_Array_Convex_4x0603","3",""
"SW1","Reset","Button_Switch_SMD:SW_SPST_SKQG_WithStem","1",""
"SW2","Boot","Button_Switch_SMD:SW_SPST_SKQG_WithStem","1",""
"SW3","ADDRESS","Button_Switch_SMD:SW_DIP_SPSTx04_Slide_6.7x11.72mm_W8.61mm_P2.54mm_LowProfile","1",""
"TP3","J9_IOSTB","TestPoint:TestPoint_Pad_D1.5mm","1",""
"TP4","J9_NBRESET","TestPoint:TestPoint_Pad_D1.5mm","1",""
"TP5","J9_D0","TestPoint:TestPoint_Pad_D1.5mm","1",""
"TP6","J9_A0","TestPoint:TestPoint_Pad_D1.5mm","1",""
"U1","ADM3483","Package_SO:SOIC-8_3.9x4.9mm_P1.27mm","1","http://www.icbase.com/pdf/SPX/SPX00480106.pdf"
"U3","RP2354B","Package_DFN_QFN:QFN-80-1EP_10x10mm_P0.4mm_EP3.4x3.4mm","1",""
"U4","LMV321","Package_TO_SOT_SMD:SOT-23-5","1","http://www.ti.com/lit/ds/symlink/lmv324.pdf"
"U5","SN74AHCT1G125","Package_TO_SOT_SMD:SOT-23-5","1","http://www.ti.com/lit/sg/scyt129e/scyt129e.pdf"
"U6","AP2112K-3.3","Package_TO_SOT_SMD:SOT-23-5","1","https://www.diodes.com/assets/Datasheets/AP2112.pdf"
"U7","SN74LVC8T245","Package_SO:TSSOP-24_4.4x7.8mm_P0.65mm","1","https://www.ti.com/lit/ds/symlink/sn74lvc8t245.pdf"
"U8","74AHCT541","Package_SO:TSSOP-20_4.4x6.5mm_P0.65mm","1","https://www.ti.com/lit/ds/symlink/sn74ahct541.pdf"
"Y1","12MHz,18pF","Crystal:Crystal_SMD_3225-4Pin_3.2x2.5mm","1",""

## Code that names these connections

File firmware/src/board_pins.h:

// RP2354B GPIO map of the SAM CPU board.
//
// Source of truth: hardware/kicad/sam_cpu/mcu.kicad_sch (PR #4) and
// hardware/kicad/README.md "RP2354B GPIO map".
// Keep this file in step with the schematic.
//
// SPDX-License-Identifier: GPL-3.0-or-later
#pragma once

// ---- PIO0, GPIO base 0: SAM IO bus on J9 ---------------------------------
// D0-D7 then A0-A3 on consecutive pins, so one `out pins, 12` drives a whole
// address + data word.
#define PIN_BUS_D0 0          // D0-D7 = GPIO0-7
#define PIN_BUS_A0 8          // A0-A3 = GPIO8-11
#define PIN_BUS_IOSTB 12      // side-set bit 0, active low (through 74AHCT541)
#define PIN_BUS_DIR 13        // side-set bit 1, SN74LVC8T245 DIR: 1 = RP2354B drives J9
#define PIN_NBRESET_DRV 14    // high = 2N7002 on = IO board held in reset (pulled up at boot)
#define PIN_BUS_OE_N 15       // low = both J9 buffers enabled (pulled up at boot)

// ---- PIO1, GPIO base 16: switch shift chain ------------------------------
#define PIN_SW_CLK 16         // shared 74HC165 / 74HC595 shift clock (side-set bit 0)
#define PIN_SW_LOAD_N 17      // 165 parallel load (low) + 595 latch (rising edge) (side-set bit 1)
#define PIN_SW_DATA 18        // serial data in from the 165 chain (U30 QH)
#define PIN_STB_DATA 19       // serial data out to the 595 chain (U31 SER)

// GPIO20-36 were the DMD outputs (J5 and two HUB75), removed from the board:
// the Pi drives the display. The board now puts an RS485 port on GPIO20-22
// (UART1 TX, RX, DE); the firmware does not use it yet.

// ---- Misc -----------------------------------------------------------------
#define PIN_RP_IRQ_N 37       // to the Pi: low = "switch changed, poll me"
#define PIN_GI_PWM 38         // J18 GI dimmer board, PWM (slice 11 A)
#define PIN_AMP_MUTE 39       // audio amplifier mute, high = muted (pull-down on the board)

// GPIO40-42 (frame SPI from the Pi) have no use now that the DMD is gone.

#define PIN_SPARE_43 43
#define PIN_LINK_UART_TX 44   // UART0 TX (function 2 on GPIO44)
#define PIN_LINK_UART_RX 45   // UART0 RX
#define PIN_VMON_5V 46        // ADC channel 6
#define PIN_VMON_12V 47       // ADC channel 7

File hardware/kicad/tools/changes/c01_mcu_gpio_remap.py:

"""Change 01 (2026-10-06): two HD DMD panels. Re-assign RP2354B GPIOs on the MCU sheet, in place.
Pin map: /mnt/project-files/hardware/dmd_two_panel_pin_proposal.md (17-signal variant)."""
import sys, os, re
HERE = os.path.dirname(os.path.abspath(__file__))
sys.path.insert(0, HERE); sys.path.insert(0, os.path.dirname(HERE))
import schlib as L
import design2
from kigen import pin_outward

F = os.path.join(HERE, '..', '..', 'sam_cpu', 'mcu.kicad_sch')
NEW = {20: 'DMD_D0', 21: 'DMD_D1', 22: 'DMD_D2', 23: 'DMD_D3', 24: 'DMD_D4', 25: 'DMD_D5', 26: 'DMD_D6',
       27: 'DMD_D7', 28: 'DMD_D8', 29: 'DMD_D9', 30: 'DMD_D10', 31: 'DMD_D11',
       32: 'DMD_CLK', 33: 'DMD_LAT', 34: 'DMD_OE', 35: 'DMD_A', 36: 'DMD_B',
       37: 'RP_IRQ_N', 38: 'GI_PWM', 39: 'AMP_MUTE', 40: 'FRAME_MOSI', 41: 'FRAME_CS_N', 42: 'FRAME_SCK',
       44: 'RP_UART_TX', 45: 'RP_UART_RX', 46: 'VMON_5V', 47: 'VMON_12V'}

page = [p for p in design2.PAGES if p.filename == 'mcu.kicad_sch'][0]
u4 = [q for q in page.parts if q.ref == 'U4'][0]
gpio_pin = {int(p['name'].split('/')[0][4:]): p['number'] for p in u4.sd.pins if p['name'].startswith('GPIO')}


def outward(part, num):
    p = part.pin(num)
    d = pin_outward(p['angle'], part.rot)
    if part.mirror == 'y':
        d = {'L': 'R', 'R': 'L'}.get(d, d)
    return d


# every pin end on the sheet, to find what a removed wire used to connect
ends = []
for part in page.parts:
    for p in part.unit_pins():
        if part.lib_id.startswith('power:'):
            continue
        ends.append((part, p['number'], part.pin_pos(p['number'])))

text = open(F).read()
head, blocks, foot = L.split(text)
drop, add = set(), []
for g, new in sorted(NEW.items()):
    num = gpio_pin[g]
    P = u4.pin_pos(num)
    d = outward(u4, num)
    old = u4.nets[num]
    if old == new:
        continue
    nc = [i for i, b in enumerate(blocks) if L.kind(b) == 'no_connect' and L.same(L.at(b)[:2], P)]
    if nc:
        drop |= set(nc)
        L.stub_label(add, P, d, new)
        continue
    q = (P[0] + L.DV[d][0] * L.STUB, P[1] + L.DV[d][1] * L.STUB)
    lab = [i for i, b in enumerate(blocks) if L.kind(b) == 'global_label' and L.same(L.at(b)[:2], q)]
    if lab:
        i = lab[0]
        blocks[i] = blocks[i].replace('(global_label "%s"' % old, '(global_label "%s"' % new, 1)
        continue
    # routed with wires on this sheet: remove the run, label both ends
    ws, js, ls, pts = L.wire_component(blocks, P)
    assert ws, (g, old)
    drop |= ws | js | ls
    L.stub_label(add, P, d, new)
    for part, n2, e in ends:
        if part is u4 and n2 == num:
            continue
        if any(L.same(e, x) for x in pts):
            d2 = outward(part, n2)
            if part.ref == 'R17':      # keep LED_STATUS clear of the GPIO46 label on the same row
                k = (e[0] + 2.54, e[1]); m = (k[0], k[1] + 5.08)
                add += [L.wire(e, k), L.wire(k, m), L.glabel(old, m, 'D')]
            elif part.ref == 'R18':    # step up so the label clears R19 next to it
                k = (e[0], e[1] - 2.54)
                add += [L.wire(e, k), L.glabel(old, k, 'R')]
            else:
                L.stub_label(add, e, d2, old)
            print('GPIO%d: %s moved off, %s.%s keeps %s by label' % (g, old, part.ref, n2, old))
# GPIO43 becomes free; old users of 43 none. Pins left without a net get a no-connect
blocks = [b for i, b in enumerate(blocks) if i not in drop] + add
s = L.join(head, blocks, foot)
s = s.replace('PIO2 DMD on GPIO21-27, GPIO31 coin door memory protect.',
              'PIO2 drives two HD DMD panels on GPIO20-36 (data 20-31, CLK, LAT, OE, A, B); the original DMD (J5) shares GPIO20-26.'
              '\\nFrames from the Pi on SPI1 (GPIO40-42), UART0 on GPIO44-45, ADC monitors on GPIO46-47, GPIO43 spare.'
              ' Coin door, status LED and GI_SPARE moved onto the switch chain.')
open(F, 'w').write(s)
print('mcu: removed', len(drop), 'items, added', len(add))

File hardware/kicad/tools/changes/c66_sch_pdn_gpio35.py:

"""c66 (schematic): AMP_PDN also driven by the RP2354B (Vincent's card, 2026-11-12: I2C + PDN, 3 wires).

A clean corridor exists from U4 pin 44 (GPIO35): F stub to a via east of the pin, In2 under slow lines only, then
B / F to the AMP_PDN via (c66b board). LINE_DET stays on the 74HC157 only.
- mcu sheet: U4 pin 44 (GPIO35) no-connect -> AMP_PDN.
- audio sheet: R190 10k pull-up kept (amplifiers leave shutdown by themselves while GPIO35 is an input); C158 becomes
  100 nF (1 ms) so the GPIO drives a small load. Firmware: GPIO35 low = shutdown / hard reset, input = run.
Usage: c66_sch_pdn_gpio35.py project_dir"""
import os, re, sys
src = open(os.path.join(os.path.dirname(os.path.abspath(__file__)), 'c62_sch_audio_tas5805m.py')).read()
exec(src[:src.index('# capacitor references')])     # helpers only

p = os.path.join(d, 'mcu.kicad_sch'); s = open(p).read()
m = re.search(r'\n\t\(no_connect\n\t\t\(at 208.28 187.96\)', s); assert m
s = s[:m.start()] + s[block(s, m.start() + 2):]
add = wire((208.28, 187.96), (213.36, 187.96)) + glabel('AMP_PDN', 213.36, 187.96, 0, 'output')
k = s.rstrip().rindex('\n)') + 1
s = s[:k] + add + s[k:]
open(p, 'w').write(s)

p = os.path.join(d, 'audio.kicad_sch'); s = open(p).read()
s = replace_once(s, '(text "Amplifier control: RP2354B I2C1 (GPIO38 SDA / GPIO39 SCL), PDN by RC"',
                 '(text "Amplifier control: RP2354B I2C1 (GPIO38 SDA / GPIO39 SCL), PDN (GPIO35 + RC)"')
s = replace_once(s, '(text "AMP_PDN rises 10 ms after +3V3 (10k / 1 uF). The RP2354B resets both amplifiers\\nover I2C (0x01),',
                 '(text "AMP_PDN rises 1 ms after +3V3 (10k / 100 nF) while GPIO35 is an input. GPIO35 low = hard reset /\\nshutdown; the RP2354B also resets over I2C (0x01),')
i = s.index('(property "Reference" "C158"'); j = s.rindex('\n\t(symbol', 0, i); e = block(s, j + 2)
r = s[j:e]
r = replace_once(r, '(property "Value" "1uF"', '(property "Value" "100nF"')
r = replace_once(r, '"%s"' % D_1U, '"%s"' % D_100N)
s = s[:j] + r + s[e:]
open(p, 'w').write(s)
print('ok')
